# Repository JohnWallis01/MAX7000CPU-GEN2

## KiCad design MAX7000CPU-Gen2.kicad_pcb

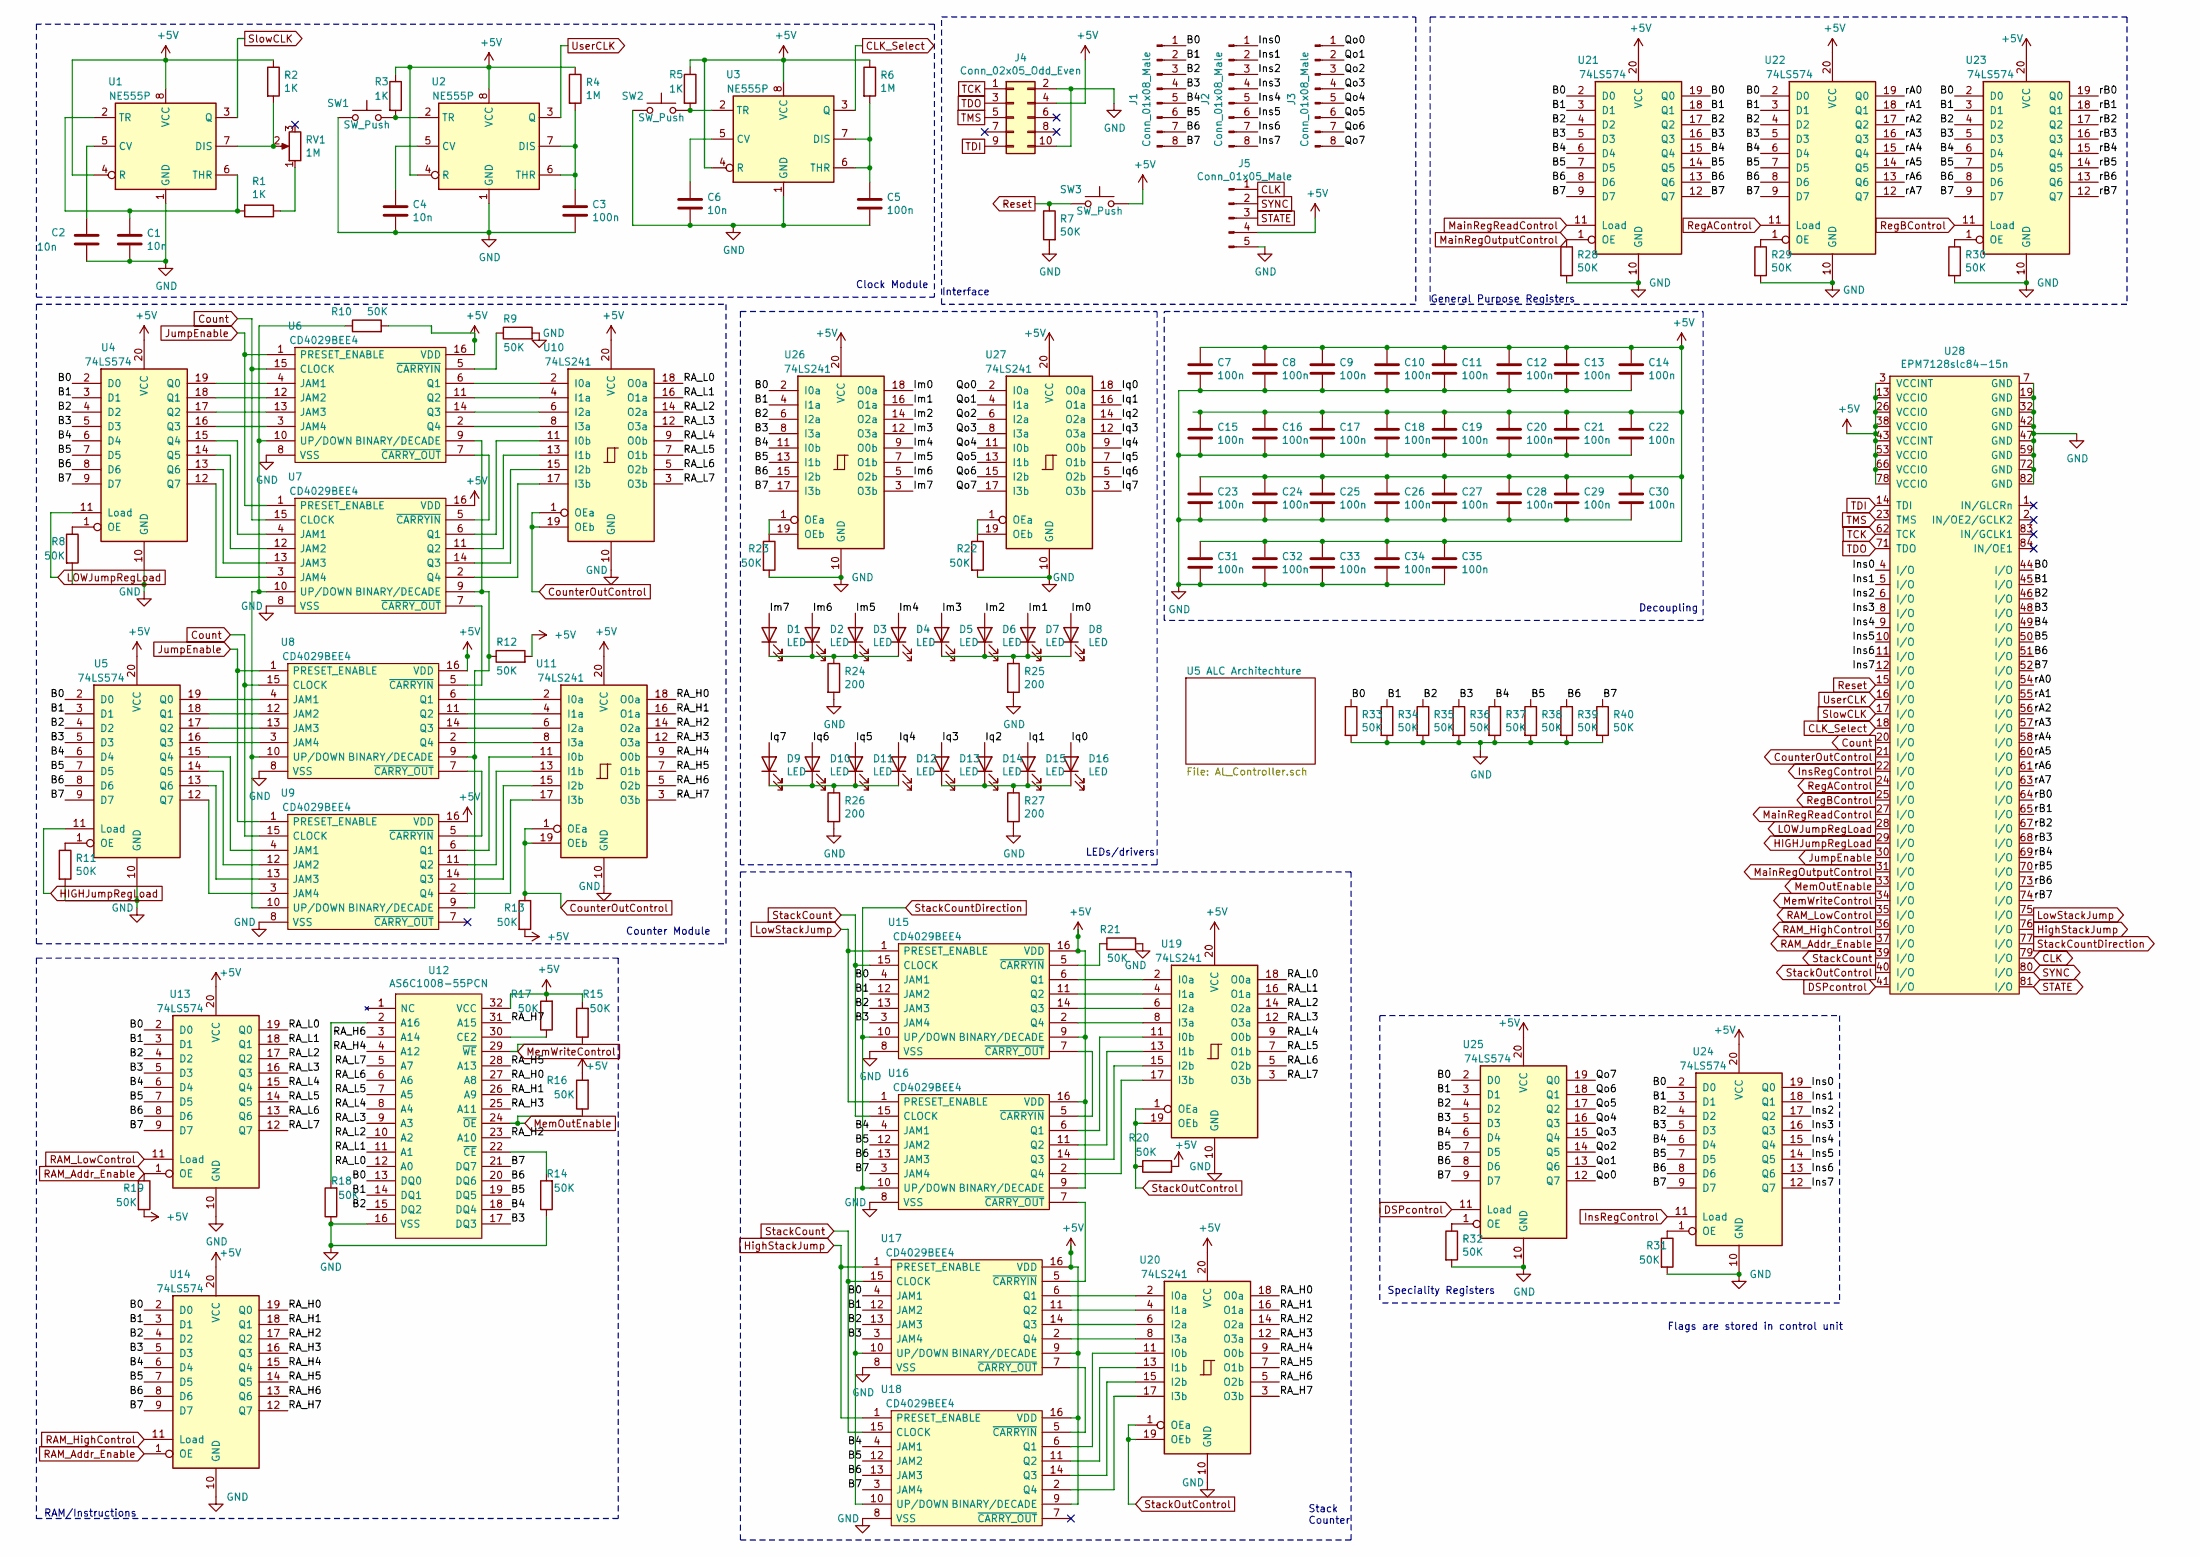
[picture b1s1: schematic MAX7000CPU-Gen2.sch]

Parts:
C1, C2, C4, C6: 10n; C_Disc_D5.0mm_W2.5mm_P2.50mm
C3, C5: 100n; C_Disc_D5.0mm_W2.5mm_P2.50mm
C7, C8, C9, C10, C11, C12, C13, C14, C15, C16, C17, C18, C19, C20, C21, C22, C23, C24, C25, C26, C27, C28, C29, C30, C31, C32, C33, C34, C35: 100n; C_0805_2012Metric_Pad1.18x1.45mm_HandSolder
D1, D2, D3, D4, D5, D6, D7, D8, D9, D10, D11, D12, D13, D14, D15, D16: LED; LED_D3.0mm
J1, J2, J3: Conn_01x08_Male; PinHeader_1x08_P2.54mm_Vertical
J4: Conn_02x05_Odd_Even; PinHeader_2x05_P2.54mm_Vertical
J5: Conn_01x05_Male; PinHeader_1x05_P2.54mm_Vertical
R1, R2, R3, R5: 1K; R_Axial_DIN0207_L6.3mm_D2.5mm_P7.62mm_Horizontal
R4, R6: 1M; R_Axial_DIN0207_L6.3mm_D2.5mm_P7.62mm_Horizontal
R7, R8, R9, R10, R11, R12, R13, R14, R15, R16, R17, R18, R19, R20, R21, R22, R23, R28, R29, R30, R31, R32, R33, R34, R35, R36, R37, R38, R39, R40: 50K; R_Axial_DIN0207_L6.3mm_D2.5mm_P7.62mm_Horizontal
R24, R25, R26, R27: 200; R_Axial_DIN0207_L6.3mm_D2.5mm_P7.62mm_Horizontal
RV1: 1M; SIP460W50P254L970H980Q3P
SW1, SW2, SW3: SW_Push; SW_PUSH_6mm
U1, U2, U3: NE555P; DIP-8_W7.62mm
U4, U5, U13, U14, U21, U22, U23, U24, U25: 74LS574; DIP-20_W7.62mm
U6, U7, U8, U9, U15, U16, U17, U18: CD4029BEE4; DIP-16_W7.62mm; Mouser Part Number 595-CD4029BEE4
U10, U11, U19, U20, U26, U27: 74LS241; DIP-20_W7.62mm
U12: AS6C1008-55PCN; DIP-32_W15.24mm; Mouser Part Number 913-AS6C1008-55PCN
U28: EPM7128slc84-15n; PLCC-84_THT-Socket

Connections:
+5V: C7.1, C8.1, C9.1, C10.1, C11.1, C12.1, C13.1, C14.1, C15.1, C16.1, C17.1, C18.1, C19.1, C20.1, C21.1, C22.1, C23.1, C24.1, C25.1, C26.1, C27.1, C28.1, C29.1, C30.1, C31.1, C32.1, C33.1, C34.1, C35.1, J4.4, J5.4, R2.1, R3.1, R4.1, R5.1, R6.1, R10.2, R12.2, R13.2, R15.2, R16.2, R17.2, R19.2, R20.2, SW3.2, U1.4 (R), U1.8 (VCC), U2.4 (R), U2.8 (VCC), U3.4 (R), U3.8 (VCC), U4.20 (VCC), U5.20 (VCC), U6.16 (VDD), U7.16 (VDD), U8.16 (VDD), U9.16 (VDD), U10.20 (VCC), U11.20 (VCC), U12.32 (VCC), U13.20 (VCC), U14.20 (VCC), U15.9 (BINARY/DECADE), U15.16 (VDD), U16.9 (BINARY/DECADE), U16.16 (VDD), U17.9 (BINARY/DECADE), U17.16 (VDD), U18.9 (BINARY/DECADE), U18.16 (VDD), U19.20 (VCC), U20.20 (VCC), U21.20 (VCC), U22.20 (VCC), U23.20 (VCC), U24.20 (VCC), U25.20 (VCC), U26.20 (VCC), U27.20 (VCC), U28.3 (VCCINT), U28.13 (VCCIO), U28.26 (VCCIO), U28.38 (VCCIO), U28.43 (VCCINT), U28.53 (VCCIO), U28.66 (VCCIO), U28.78 (VCCIO)
/B0: J1.1, R33.1, U4.2 (D0), U5.2 (D0), U12.13 (DQ0), U13.2 (D0), U14.2 (D0), U15.4 (JAM1), U17.4 (JAM1), U21.2 (D0), U21.19 (Q0), U22.2 (D0), U23.2, U24.2, U25.2 (D0), U26.2 (I0a), U28.44 (I/O); also elsewhere on the board
/B1: J1.2, R34.1, U4.3 (D1), U5.3 (D1), U12.14 (DQ1), U13.3 (D1), U14.3 (D1), U15.12 (JAM2), U17.12 (JAM2), U21.3 (D1), U21.18 (Q1), U22.3 (D1), U23.3 (GND), U24.3 (GND), U25.3 (D1), U26.4 (I1a), U28.45 (I/O)
/B2: J1.3, R35.1, U4.4 (D2), U5.4 (D2), U12.15 (DQ2), U13.4 (D2), U14.4 (D2), U15.13 (JAM3), U17.13 (JAM3), U21.4 (D2), U21.17 (Q2), U22.4 (D2), U23.4, U24.4, U25.4 (D2), U26.6 (I2a), U28.46 (I/O); also elsewhere on the board
/B3: J1.4, R36.1, U4.5 (D3), U5.5 (D3), U12.17 (DQ3), U13.5 (D3), U14.5 (D3), U15.3 (JAM4), U17.3 (JAM4), U21.5 (D3), U21.16 (Q3), U22.5 (D3), U23.5 (VCC), U24.5 (VCC), U25.5 (D3), U26.8 (I3a), U28.48 (I/O)
/B4: J1.5, R37.1, U4.6 (D4), U5.6 (D4), U12.18 (DQ4), U13.6 (D4), U14.6 (D4), U16.4 (JAM1), U18.4 (JAM1), U21.6 (D4), U21.15 (Q4), U22.6 (D4), U23.6 (D4), U24.6 (D4), U25.6 (D4), U26.11 (I0b), U28.49 (I/O)
/B5: J1.6, R38.1, U4.7 (D5), U5.7 (D5), U12.19 (DQ5), U13.7 (D5), U14.7 (D5), U16.12 (JAM2), U18.12 (JAM2), U21.7 (D5), U21.14 (Q5), U22.7 (D5), U23.7 (D5), U24.7 (D5), U25.7 (D5), U26.13 (I1b), U28.50 (I/O)
/B6: J1.7, R39.1, U4.8 (D6), U5.8 (D6), U12.20 (DQ6), U13.8 (D6), U14.8 (D6), U16.13 (JAM3), U18.13 (JAM3), U21.8 (D6), U21.13 (Q6), U22.8 (D6), U23.8 (D6), U24.8 (D6), U25.8 (D6), U26.15 (I2b), U28.51 (I/O)
/B7: J1.8, R40.1, U4.9 (D7), U5.9 (D7), U12.21 (DQ7), U13.9 (D7), U14.9 (D7), U16.3 (JAM4), U18.3 (JAM4), U21.9 (D7), U21.12 (Q7), U22.9 (D7), U23.9 (D7), U24.9 (D7), U25.9 (D7), U26.17 (I3b), U28.52 (I/O)
/Im0: D8.2 (A), U26.18 (O0a)
/Im1: D7.2 (A), U26.16 (O1a)
/Im2: D6.2 (A), U26.14 (O2a)
/Im3: D5.2 (A), U26.12 (O3a)
/Im4: D4.2 (A), U26.9 (O0b)
/Im5: D3.2 (A), U26.7 (O1b)
/Im6: D2.2 (A), U26.5 (O2b)
/Im7: D1.2 (A), U26.3 (O3b)
/Ins0: J2.1, U24.19 (Q0), U28.4 (I/O)
/Ins1: J2.2, U24.18 (Q1), U28.5 (I/O)
/Ins2: J2.3, U24.17 (Q2), U28.6 (I/O)
/Ins3: J2.4, U24.16 (Q3), U28.8 (I/O)
/Ins4: J2.5, U24.15 (Q4), U28.9 (I/O)
/Ins5: J2.6, U24.14 (Q5), U28.10 (I/O)
/Ins6: J2.7, U24.13 (Q6), U28.11 (I/O)
/Ins7: J2.8, U24.12 (Q7), U28.12 (I/O)
/Iq0: D16.2 (A), U27.18 (O0a)
/Iq1: D15.2 (A), U27.16 (O1a)
/Iq2: D14.2 (A), U27.14 (O2a)
/Iq3: D13.2 (A), U27.12 (O3a)
/Iq4: D12.2 (A), U27.9 (O0b)
/Iq5: D11.2 (A), U27.7 (O1b)
/Iq6: D10.2 (A), U27.5 (O2b)
/Iq7: D9.2 (A), U27.3 (O3b)
/Qo0: J3.1, U25.12 (Q7), U27.2 (I0a)
/Qo1: J3.2, U25.13 (Q6), U27.4 (I1a)
/Qo2: J3.3, U25.14 (Q5), U27.6 (I2a)
/Qo3: J3.4, U25.15 (Q4), U27.8 (I3a)
/Qo4: J3.5, U25.16 (Q3), U27.11 (I0b)
/Qo5: J3.6, U25.17 (Q2), U27.13 (I1b)
/Qo6: J3.7, U25.18 (Q1), U27.15 (I2b)
/Qo7: J3.8, U25.19 (Q0), U27.17 (I3b)
/RA_H0: U11.18 (O0a), U12.27 (A8), U14.19 (Q0), U20.18 (O0a)
/RA_H1: U11.16 (O1a), U12.26 (A9), U14.18 (Q1), U20.16 (O1a)
/RA_H2: U11.14 (O2a), U12.23 (A10), U14.17 (Q2), U20.14 (O2a)
/RA_H3: U11.12 (O3a), U12.25 (A11), U14.16 (Q3), U20.12 (O3a)
/RA_H4: U11.9 (O0b), U12.4 (A12), U14.15 (Q4), U20.9 (O0b)
/RA_H5: U11.7 (O1b), U12.28 (A13), U14.14 (Q5), U20.7 (O1b)
/RA_H6: U11.5 (O2b), U12.3 (A14), U14.13 (Q6), U20.5 (O2b)
/RA_H7: U11.3 (O3b), U12.31 (A15), U14.12 (Q7), U20.3 (O3b)
/RA_L0: U10.18 (O0a), U12.12 (A0), U13.19 (Q0), U19.18 (O0a)
/RA_L1: U10.16 (O1a), U12.11 (A1), U13.18 (Q1), U19.16 (O1a)
/RA_L2: U10.14 (O2a), U12.10 (A2), U13.17 (Q2), U19.14 (O2a)
/RA_L3: U10.12 (O3a), U12.9 (A3), U13.16 (Q3), U19.12 (O3a)
/RA_L4: U10.9 (O0b), U12.8 (A4), U13.15 (Q4), U19.9 (O0b)
/RA_L5: U10.7 (O1b), U12.7 (A5), U13.14 (Q5), U19.7 (O1b)
/RA_L6: U10.5 (O2b), U12.6 (A6), U13.13 (Q6), U19.5 (O2b)
/RA_L7: U10.3 (O3b), U12.5 (A7), U13.12 (Q7), U19.3 (O3b)
/rA0: U22.19 (Q0), U28.54 (I/O)
/rA1: U22.18 (Q1), U28.55 (I/O)
/rA2: U22.17 (Q2), U28.56 (I/O)
/rA3: U22.16 (Q3), U28.57 (I/O)
/rA4: U22.15 (Q4), U28.58 (I/O)
/rA5: U22.14 (Q5), U28.60 (I/O)
/rA6: U22.13 (Q6), U28.61 (I/O)
/rA7: U22.12 (Q7), U28.63 (I/O)
/rB0: U23.19 (Q0), U28.64 (I/O)
/rB1: U23.18 (Q1), U28.65 (I/O)
/rB2: U23.17 (Q2), U28.67 (I/O)
/rB3: U23.16 (Q3), U28.68 (I/O)
/rB4: U23.15 (Q4), U28.69 (I/O)
/rB5: U23.14 (Q5), U28.70 (I/O)
/rB6: U23.13 (Q6), U28.73 (I/O)
/rB7: U23.12 (Q7), U28.74 (I/O)
CLK: J5.1, U28.79 (I/O)
CLK_Select: U3.3 (Q), U28.18 (I/O)
Count: U6.15 (CLOCK), U7.15 (CLOCK), U8.15 (CLOCK), U9.15 (CLOCK), U28.20 (I/O)
CounterOutControl: R13.1, U10.1 (OEa), U10.19 (OEb), U11.1 (OEa), U11.19 (OEb), U28.21 (I/O)
DSPcontrol: U25.11 (Load), U28.41 (I/O)
GND: C1.2, C2.2, C3.2, C4.2, C5.2, C6.2, C7.2, C8.2, C9.2, C10.2, C11.2, C12.2, C13.2, C14.2, C15.2, C16.2, C17.2, C18.2, C19.2, C20.2, C21.2, C22.2, C23.2, C24.2, C25.2, C26.2, C27.2, C28.2, C29.2, C30.2, C31.2, C32.2, C33.2, C34.2, C35.2, J4.2, J4.10, J5.5, R7.2, R8.2, R9.2, R11.2, R14.1, R18.1, R21.2, R22.2, R23.2, R24.2, R25.2, R26.2, R27.2, R28.2, R29.2, R30.2, R31.2, R32.2, R33.2, R34.2, R35.2, R36.2, R37.2, R38.2, R39.2, R40.2, SW1.1, SW2.1, U1.1 (GND), U2.1 (GND), U3.1 (GND), U4.10 (GND), U5.10 (GND), U6.8 (VSS), U7.8 (VSS), U8.8 (VSS), U9.8 (VSS), U10.10 (GND), U11.10 (GND), U12.16 (VSS), U13.10 (GND), U14.10 (GND), U15.8 (VSS), U16.8 (VSS), U17.8 (VSS), U18.8 (VSS), U19.10 (GND), U20.10 (GND), U21.10 (GND), U22.10 (GND), U23.10 (GND), U24.10 (GND), U25.10 (GND), U26.10 (GND), U27.10 (GND), U28.7 (GND), U28.19 (GND), U28.32 (GND), U28.42 (GND), U28.47 (GND), U28.59 (GND), U28.72 (GND), U28.82 (GND)
HIGHJumpRegLoad: U5.11 (Load), U28.29 (I/O)
HighStackJump: U17.1 (PRESET_ENABLE), U18.1 (PRESET_ENABLE), U28.76 (I/O)
InsRegControl: U24.11 (Load), U28.22 (I/O)
JumpEnable: U6.1 (PRESET_ENABLE), U7.1 (PRESET_ENABLE), U8.1 (PRESET_ENABLE), U9.1 (PRESET_ENABLE), U28.30 (I/O)
LOWJumpRegLoad: U4.11 (Load), U28.28 (I/O)
LowStackJump: U15.1 (PRESET_ENABLE), U16.1 (PRESET_ENABLE), U28.75 (I/O)
MainRegOutputControl: R28.1, U21.1 (OE), U28.31 (I/O)
MainRegReadControl: U21.11 (Load), U28.27 (I/O)
MemOutEnable: R16.1, U12.24 (~OE), U28.33 (I/O)
MemWriteControl: R15.1, U12.29 (~WE), U28.34 (I/O)
unnamed: C1.1, R1.2, U1.2 (TR), U1.6 (THR)
unnamed: C2.1, U1.5 (CV)
unnamed: C3.1, R4.2, U2.6 (THR), U2.7 (DIS)
unnamed: C4.1, U2.5 (CV)
unnamed: C5.1, R6.2, U3.6 (THR), U3.7 (DIS)
unnamed: C6.1, U3.5 (CV)
unnamed: D1.1 (K), D2.1 (K), D3.1 (K), D4.1 (K), R24.1
unnamed: D5.1 (K), D6.1 (K), D7.1 (K), D8.1 (K), R25.1
unnamed: D9.1 (K), D10.1 (K), D11.1 (K), D12.1 (K), R26.1
unnamed: D13.1 (K), D14.1 (K), D15.1 (K), D16.1 (K), R27.1
unnamed: R1.1, RV1.1
unnamed: R2.2, RV1.2, U1.7 (DIS)
unnamed: R3.2, SW1.2, U2.2 (TR)
unnamed: R5.2, SW2.2, U3.2 (TR)
unnamed: R8.1, U4.1 (OE)
unnamed: R9.1, U6.5 (~CARRYIN)
unnamed: R10.1, U6.10 (UP/DOWN), U7.10 (UP/DOWN), U8.10 (UP/DOWN), U9.10 (UP/DOWN)
unnamed: R11.1, U5.1 (OE)
unnamed: R12.1, U6.9 (BINARY/DECADE), U7.9 (BINARY/DECADE), U8.9 (BINARY/DECADE), U9.9 (BINARY/DECADE)
unnamed: R14.2, U12.22 (~CE)
unnamed: R17.1, U12.30 (CE2)
unnamed: R18.2, U12.2 (A16)
unnamed: R21.1, U15.5 (~CARRYIN)
unnamed: R22.1, U27.1 (OEa), U27.19 (OEb)
unnamed: R23.1, U26.1 (OEa), U26.19 (OEb)
unnamed: R29.1, U22.1 (OE)
unnamed: R30.1, U23.1
unnamed 119: R31.1, U24.1; also elsewhere on the board
unnamed: R32.1, U25.1 (OE)
unnamed: U4.12 (Q7), U7.3 (JAM4)
unnamed: U4.13 (Q6), U7.13 (JAM3)
unnamed: U4.14 (Q5), U7.12 (JAM2)
unnamed: U4.15 (Q4), U7.4 (JAM1)
unnamed: U4.16 (Q3), U6.3 (JAM4)
unnamed: U4.17 (Q2), U6.13 (JAM3)
unnamed: U4.18 (Q1), U6.12 (JAM2)
unnamed: U4.19 (Q0), U6.4 (JAM1)
unnamed: U5.12 (Q7), U9.3 (JAM4)
unnamed: U5.13 (Q6), U9.13 (JAM3)
unnamed: U5.14 (Q5), U9.12 (JAM2)
unnamed: U5.15 (Q4), U9.4 (JAM1)
unnamed: U5.16 (Q3), U8.3 (JAM4)
unnamed: U5.17 (Q2), U8.13 (JAM3)
unnamed: U5.18 (Q1), U8.12 (JAM2)
unnamed: U5.19 (Q0), U8.4 (JAM1)
unnamed: U6.7 (~CARRY_OUT), U7.5 (~CARRYIN)
unnamed: U7.7 (~CARRY_OUT), U8.5 (~CARRYIN)
unnamed: U8.7 (~CARRY_OUT), U9.5 (~CARRYIN)
unnamed: U6.6 (Q1), U10.2 (I0a)
unnamed: U6.11 (Q2), U10.4 (I1a)
unnamed: U6.14 (Q3), U10.6 (I2a)
unnamed: U6.2 (Q4), U10.8 (I3a)
unnamed: U7.6 (Q1), U10.11 (I0b)
unnamed: U7.11 (Q2), U10.13 (I1b)
unnamed: U7.14 (Q3), U10.15 (I2b)
unnamed: U7.2 (Q4), U10.17 (I3b)
unnamed: U8.6 (Q1), U11.2 (I0a)
unnamed: U8.11 (Q2), U11.4 (I1a)
unnamed: U8.14 (Q3), U11.6 (I2a)
unnamed: U8.2 (Q4), U11.8 (I3a)
unnamed: U9.6 (Q1), U11.11 (I0b)
unnamed: U9.11 (Q2), U11.13 (I1b)
unnamed: U9.14 (Q3), U11.15 (I2b)
unnamed: U9.2 (Q4), U11.17 (I3b)
unnamed: U15.2 (Q4), U19.8 (I3a)
unnamed: U15.6 (Q1), U19.2 (I0a)
unnamed: U15.7 (~CARRY_OUT), U16.5 (~CARRYIN)
unnamed: U15.11 (Q2), U19.4 (I1a)
unnamed: U15.14 (Q3), U19.6 (I2a)
unnamed: U16.2 (Q4), U19.17 (I3b)
unnamed: U16.6 (Q1), U19.11 (I0b)
unnamed: U16.7 (~CARRY_OUT), U17.5 (~CARRYIN)
unnamed: U16.11 (Q2), U19.13 (I1b)
unnamed: U16.14 (Q3), U19.15 (I2b)
unnamed: U17.2 (Q4), U20.8 (I3a)
unnamed: U17.6 (Q1), U20.2 (I0a)
unnamed: U17.7 (~CARRY_OUT), U18.5 (~CARRYIN)
unnamed: U17.11 (Q2), U20.4 (I1a)
unnamed: U17.14 (Q3), U20.6 (I2a)
unnamed: U18.2 (Q4), U20.17 (I3b)
unnamed: U18.6 (Q1), U20.11 (I0b)
unnamed: U18.11 (Q2), U20.13 (I1b)
unnamed: U18.14 (Q3), U20.15 (I2b)
RAM_Addr_Enable: R19.1, U13.1 (OE), U14.1 (OE), U28.37 (I/O)
RAM_HighControl: U14.11 (Load), U28.36 (I/O)
RAM_LowControl: U13.11 (Load), U28.35 (I/O)
RegAControl: U22.11 (Load), U28.24 (I/O)
RegBControl: U23.11 (Load), U28.25 (I/O)
Reset: R7.1, SW3.1, U28.15 (I/O)
STATE: J5.3, U28.81 (I/O)
SYNC: J5.2, U28.80 (I/O)
SlowCLK: U1.3 (Q), U28.17 (I/O)
StackCount: U15.15 (CLOCK), U16.15 (CLOCK), U17.15 (CLOCK), U18.15 (CLOCK), U28.39 (I/O)
StackCountDirection: U15.10 (UP/DOWN), U16.10 (UP/DOWN), U17.10 (UP/DOWN), U18.10 (UP/DOWN), U28.77 (I/O)
StackOutControl: R20.1, U19.1 (OEa), U19.19 (OEb), U20.1 (OEa), U20.19 (OEb), U28.40 (I/O)
TCK: J4.1, U28.62 (TCK)
TDI: J4.9, U28.14 (TDI)
TDO: J4.3, U28.71 (TDO)
TMS: J4.5, U28.23 (TMS)
UserCLK: U2.3 (Q), U28.16 (I/O)

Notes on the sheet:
Clock Module
Counter Module
LEDs/drivers
General Purpose Registers
Interface
RAM/Instructions
Stack Counter
Speciality Registers
Flags are stored in control unit
Decoupling

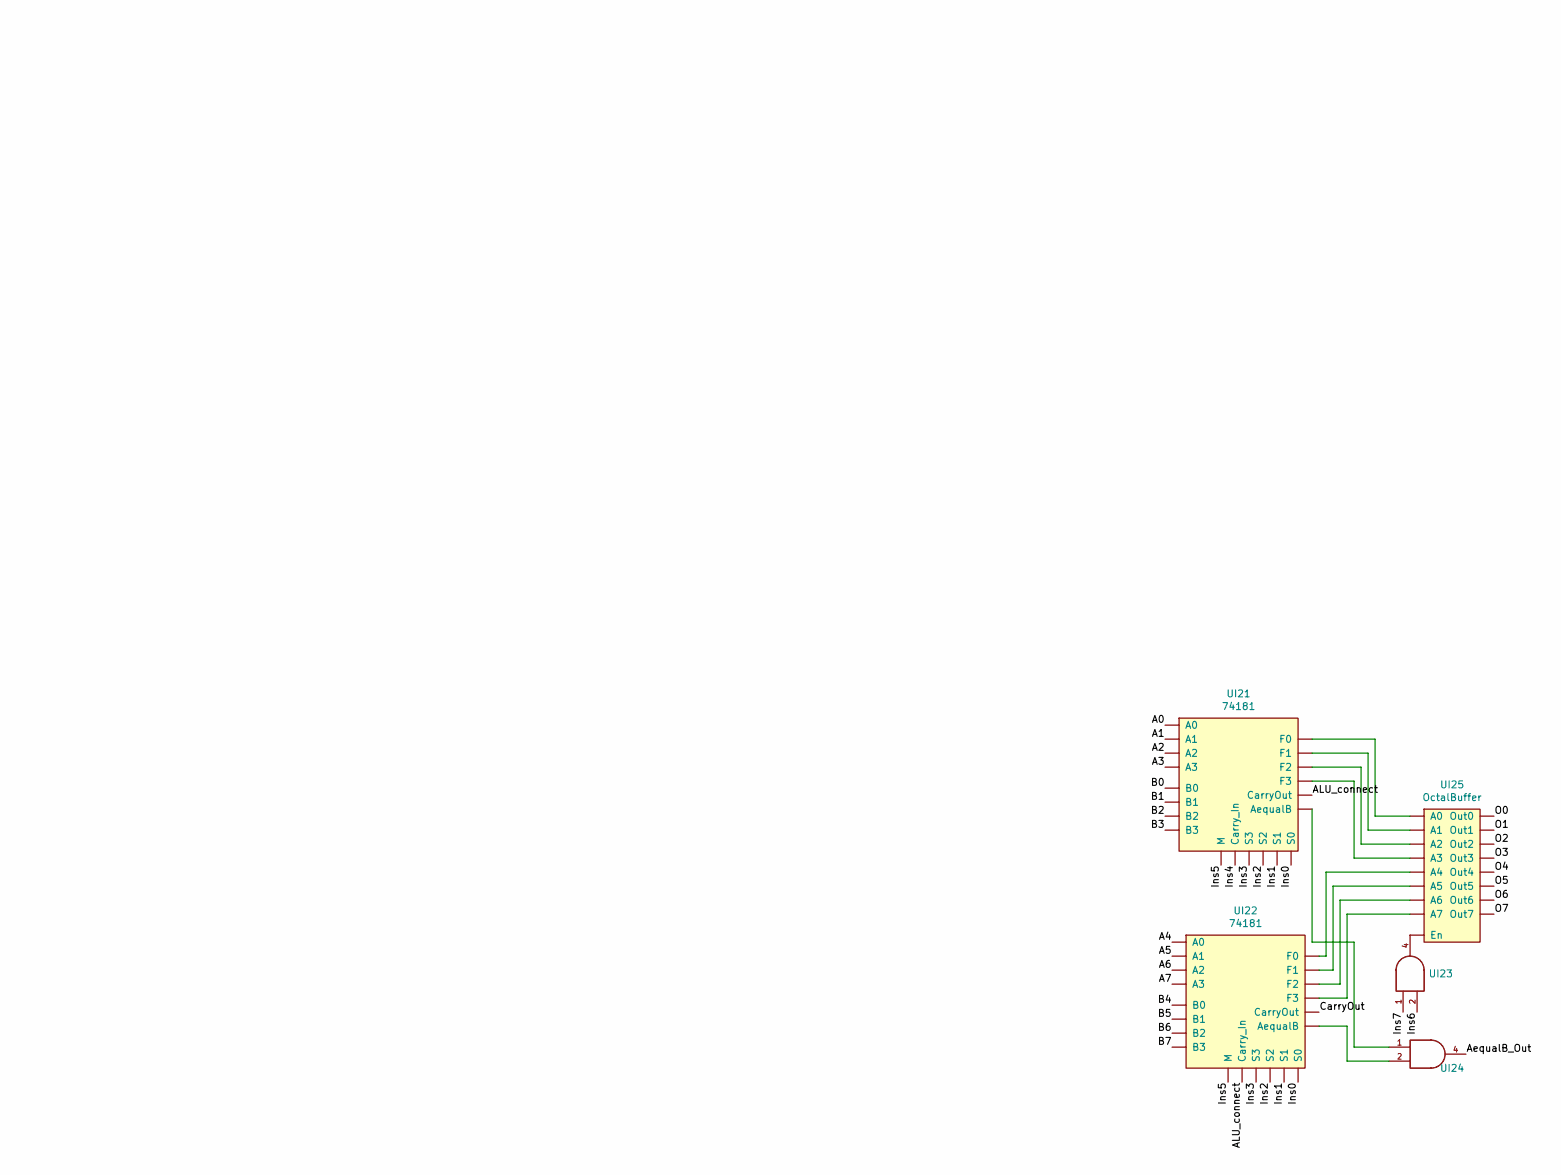
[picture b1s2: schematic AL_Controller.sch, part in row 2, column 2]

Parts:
U23: 74AHC1G08
U24: a
UI21, UI22: 74181
UI25: OctalBuffer

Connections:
/B0: U23.2, U24.2, UI22.~; also elsewhere on the board
/B1: U23.3 (GND), U24.3 (GND); also elsewhere on the board
/B2: U23.4, U24.4, UI25.~; also elsewhere on the board
/B3: U23.5 (VCC), U24.5 (VCC); also elsewhere on the board
unnamed 118: U23.1; also elsewhere on the board
unnamed 119: U24.1, UI21.~; also elsewhere on the board
unnamed: UI21.~, UI22.~, UI25.~
unnamed: UI22.~, UI25.~

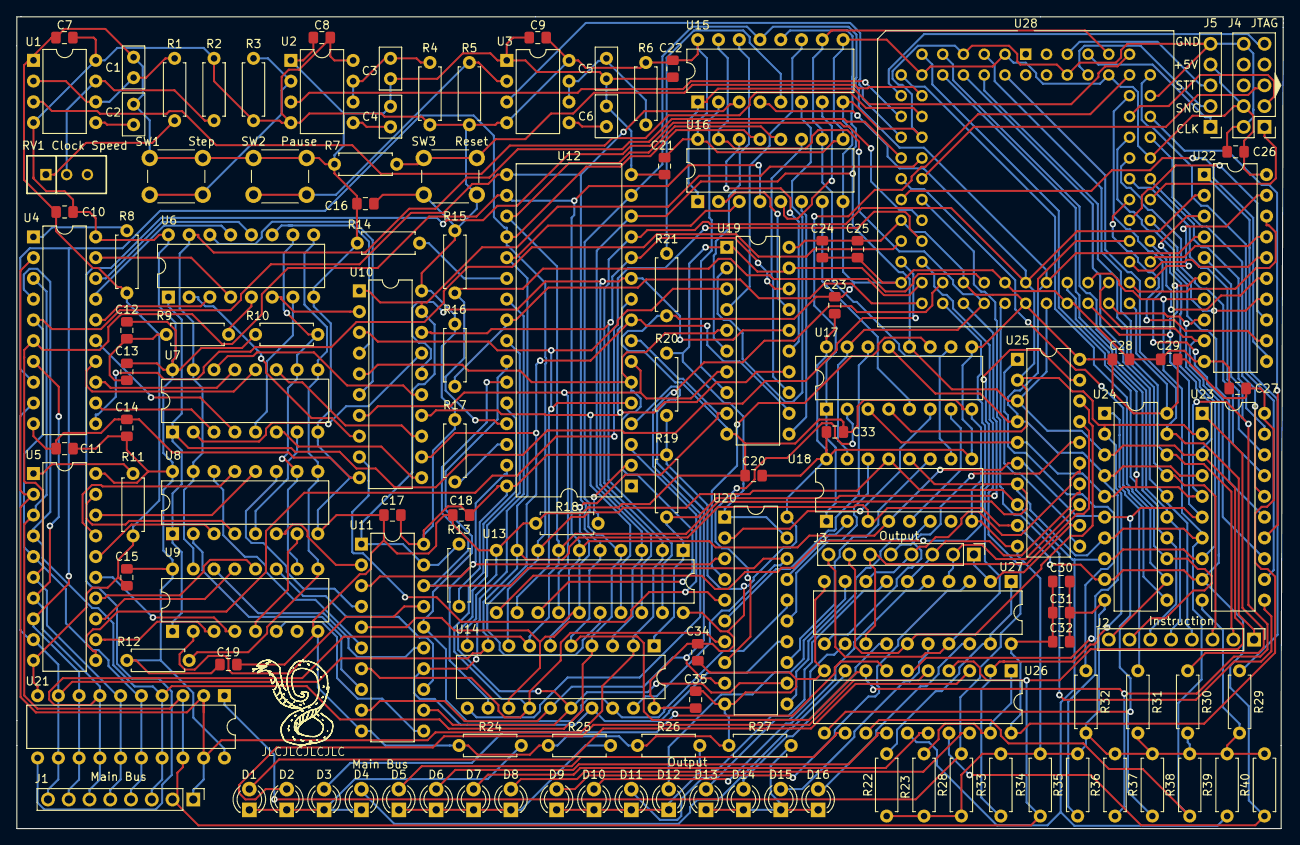
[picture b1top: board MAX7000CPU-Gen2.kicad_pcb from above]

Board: 2 copper layers, 154.9 x 99.3 mm, 128 parts (0 on the bottom side), 189 nets.

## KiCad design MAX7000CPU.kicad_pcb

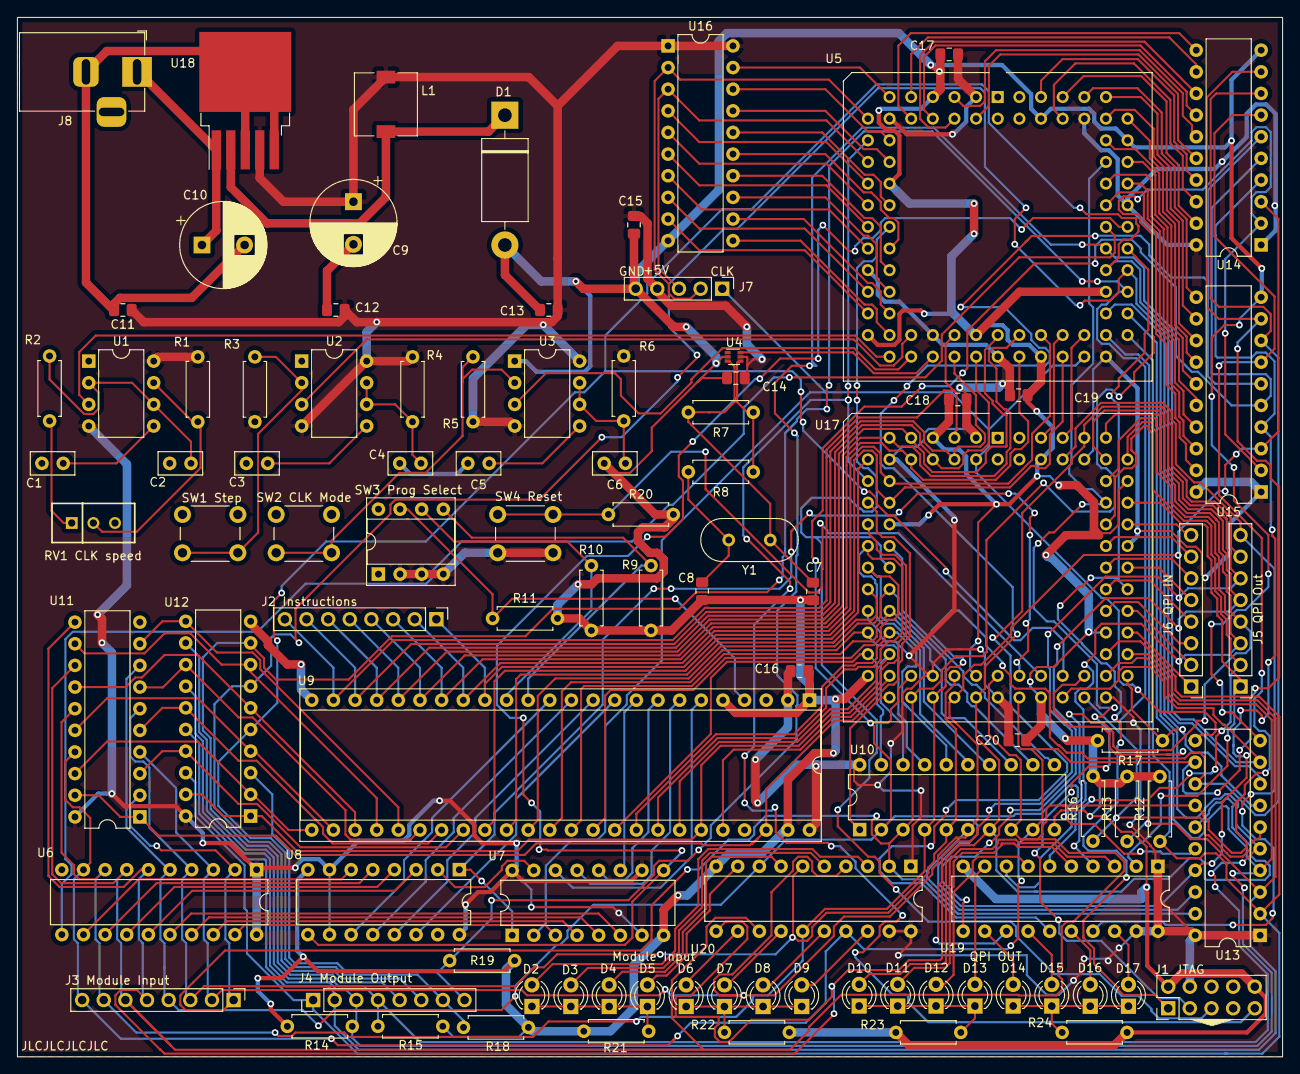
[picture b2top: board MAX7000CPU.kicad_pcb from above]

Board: 2 copper layers, 148.5 x 122.0 mm, 96 parts (0 on the bottom side), 170 nets.

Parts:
C1, C2, C3, C5: 10n; C_Disc_D5.0mm_W2.5mm_P2.50mm
C4, C6: 100n; C_Disc_D5.0mm_W2.5mm_P2.50mm
C7, C8: 32p; C_0805_2012Metric_Pad1.18x1.45mm_HandSolder
C9: 220u; CP_Radial_D10.0mm_P5.00mm
C10: 680u; CP_Radial_D10.0mm_P5.00mm
C11, C12, C13, C14, C15, C16, C17, C18, C19, C20: 100n; C_0805_2012Metric_Pad1.18x1.45mm_HandSolder
D1: 1N5822; D_DO-201AD_P15.24mm_Horizontal
D2, D3, D4, D5, D6, D7, D8, D9, D10, D11, D12, D13, D14, D15, D16, D17: LED; LED_D3.0mm
J1 JTAG: Conn_02x05_Odd_Even; PinHeader_2x05_P2.54mm_Vertical
J2 Instructions, J3 Module Input, J4 Module Output, J5 QPI Out, J6 QPI IN: Conn_01x08_Male; PinHeader_1x08_P2.54mm_Vertical
J7: Conn_01x05_Male; PinHeader_1x05_P2.54mm_Vertical
J8: Barrel_Jack; BarrelJack_Horizontal
L1: 33u; L_7.3x7.3_H3.5
R1, R2, R3, R5, R8: 1K; R_Axial_DIN0207_L6.3mm_D2.5mm_P7.62mm_Horizontal
R4, R6: 1M; R_Axial_DIN0207_L6.3mm_D2.5mm_P7.62mm_Horizontal
R7: 2.2M; R_Axial_DIN0207_L6.3mm_D2.5mm_P7.62mm_Horizontal
R9, R10, R11, R12, R13, R14, R15, R16, R17, R18, R19, R20: 50K; R_Axial_DIN0207_L6.3mm_D2.5mm_P7.62mm_Horizontal
R21, R22, R23, R24: 200; R_Axial_DIN0207_L6.3mm_D2.5mm_P7.62mm_Horizontal
RV1 CLK speed: 1M; SIP460W50P254L970H980Q3P
SW1 Step, SW2 CLK Mode, SW4 Reset: SW_Push; SW_PUSH_6mm
SW3 Prog Select: SW_DIP_x04; DIP-8_W7.62mm_Socket
U1, U2, U3: NE555P; DIP-8_W7.62mm
U4: CLVC1GX04MDRLREP; SOT-563
U5, U17: EPM7128slc84-15n; PLCC-84_THT-Socket
U6, U10, U13, U14, U15, U16: 74LS573; DIP-20_W7.62mm
U7, U8: SN74HC161N; DIP-16_W7.62mm
U9: IDT7132; DIP-48_W15.24mm_Socket
U11, U12, U19, U20: 74LS241; DIP-20_W7.62mm
U18: LM2596S-5; TO-263-5_TabPin3
Y1: Crystal; Crystal_HC49-4H_Vertical

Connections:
+5V: C9.1, C11.1, C12.1, C13.1, C14.1, C15.1, C16.1, C17.1, C18.1, C19.1, C20.1, J1 JTAG.4, J7.4, L1.1, R1.1, R3.1, R4.1, R5.1, R6.1, SW3 Prog Select.2, SW3 Prog Select.3, SW3 Prog Select.4, SW4 Reset.2, U1.4, U1.8, U2.4, U2.8, U3.4, U3.8, U4.5, U5.3, U5.13, U5.26, U5.38, U5.43, U5.53, U5.66, U5.78, U6.1, U6.20, U7.7, U7.10, U7.16, U8.7, U8.10, U8.16, U9.2, U9.48, U10.20, U11.20, U12.20, U13.1, U13.20, U14.1, U14.20, U15.1, U15.20, U16.1, U16.20, U17.3, U17.13, U17.26, U17.38, U17.43, U17.53, U17.66, U17.78, U18.4, U19.1, U19.19, U19.20, U20.1, U20.19, U20.20
/A0: U5.79, U14.19
/A1: U5.80, U14.18
/A2: U5.81, U14.17
/A3: U5.4, U14.16
/A4: U5.5, U14.15
/A5: U5.8, U14.14
/A6: U5.6, U14.13
/A7: U5.9, U14.12
/B0: U5.67, U15.19
/B1: U5.68, U15.18
/B2: U5.69, U15.17
/B3: U5.70, U15.16
/B4: U5.73, U15.15
/B5: U5.74, U15.14
/B6: U5.76, U15.13
/B7: U5.75, U15.12
/C0: U7.14, U9.6
/C1: U7.13, U9.7
/C2: U7.12, U9.8
/C3: U7.11, U9.9
/C4: U8.14, U9.10
/C5: U8.13, U9.11
/C6: U8.12, U9.12
/C7: U8.11, U9.13
/I0: J3 Module Input.1, U6.2, U10.3, U11.2, U13.19, U14.2, U15.2, U17.35, U20.2
/I1: J3 Module Input.2, U6.3, U10.6, U11.4, U13.18, U14.3, U15.3, U17.39, U20.4
/I2: J3 Module Input.3, U6.4, U10.5, U11.6, U13.17, U14.4, U15.4, U17.40, U20.6
/I3: J3 Module Input.4, U6.5, U10.2, U11.8, U13.16, U14.5, U15.5, U17.36, U20.8
/I4: J3 Module Input.5, U6.6, U10.7, U11.11, U13.15, U14.6, U15.6, U17.41, U20.11
/I5: J3 Module Input.6, U6.7, U10.8, U11.13, U13.14, U14.7, U15.7, U17.44, U20.13
/I6: J3 Module Input.7, U6.8, U10.4, U11.15, U13.13, U14.8, U15.8, U17.37, U20.15
/I7: J3 Module Input.8, U6.9, U10.9, U11.17, U13.12, U14.9, U15.9, U17.45, U20.17
/Im0: D9.2, U20.18
/Im1: D8.2, U20.16
/Im2: D7.2, U20.14
/Im3: D6.2, U20.12
/Im4: D5.2, U20.9
/Im5: D4.2, U20.7
/Im6: D3.2, U20.5
/Im7: D2.2, U20.3
/Ins0: J2 Instructions.1, U5.49, U9.16, U17.17
/Ins1: J2 Instructions.2, U5.48, U9.17, U17.15
/Ins2: J2 Instructions.3, U5.45, U9.18, U17.10
/Ins3: J2 Instructions.4, U5.46, U9.19, U17.11
/Ins4: J2 Instructions.5, U5.44, U9.20, U17.9
/Ins5: J2 Instructions.6, U5.41, U9.21, U17.8
/Ins6: J2 Instructions.7, U5.39, U9.22, U17.6
/Ins7: J2 Instructions.8, U5.40, U9.23, U17.5
/Iq0: D17.2, U19.18
/Iq1: D16.2, U19.16
/Iq2: D15.2, U19.14
/Iq3: D14.2, U19.12
/Iq4: D13.2, U19.9
/Iq5: D12.2, U19.7
/Iq6: D11.2, U19.5
/Iq7: D10.2, U19.3
/M0: U9.42, U10.18, U17.31
/M1: U9.41, U10.15, U17.20
/M2: U9.40, U10.16, U17.29
/M3: U9.39, U10.19, U17.30
/M4: U9.38, U10.14, U17.22
/M5: U9.37, U10.13, U17.27
/M6: U9.36, U10.17, U17.28
/M7: U9.35, U10.12, U17.25
/M8: U9.34, U17.24
/M9: U9.33, U17.12
/M10: U9.44, U17.34
/O0: J4 Module Output.1, R12.1, U5.54, U12.18, U13.2, U17.57
/O1: J4 Module Output.2, R13.1, U5.55, U12.16, U13.3, U17.56
/O2: J4 Module Output.3, R14.1, U5.56, U12.14, U13.4, U17.55
/O3: J4 Module Output.4, R15.1, U5.57, U12.12, U13.5, U17.52
/O4: J4 Module Output.5, R16.1, U5.58, U12.9, U13.6, U17.51
/O5: J4 Module Output.6, R17.1, U5.60, U12.7, U13.7, U17.54
/O6: J4 Module Output.7, R18.1, U5.61, U12.5, U13.8, U17.50
/O7: J4 Module Output.8, R19.1, U5.63, U12.3, U13.9, U17.49
/P1: R9.1, SW3 Prog Select.5, U9.14
/P2: R10.1, SW3 Prog Select.6, U9.15
/P3: R11.1, SW3 Prog Select.7, U9.4
/Qi0: J6 QPI IN.1, U17.58
/Qi1: J6 QPI IN.2, U17.60
/Qi2: J6 QPI IN.3, U17.61
/Qi3: J6 QPI IN.4, U17.63
/Qi4: J6 QPI IN.5, U17.64
/Qi5: J6 QPI IN.6, U17.65
/Qi6: J6 QPI IN.7, U17.67
/Qi7: J6 QPI IN.8, U17.68
/Qo0: J5 QPI Out.1, U17.70, U19.2
/Qo1: J5 QPI Out.2, U17.69, U19.4
/Qo2: J5 QPI Out.3, U17.74, U19.6
/Qo3: J5 QPI Out.4, U17.73, U19.8
/Qo4: J5 QPI Out.5, U17.75, U19.11
/Qo5: J5 QPI Out.6, U17.76, U19.13
/Qo6: J5 QPI Out.7, U17.77, U19.15
/Qo7: J5 QPI Out.8, U17.80, U19.17
A=B_FlagIn: U5.15, U16.18
A=B_Out: J7.3, U5.16, U16.3
CLK: J7.1, U5.51, U7.2, U13.11, U17.4
CLK_Select: U3.3, U5.35
CarryFlagIn: U5.11, U16.19
CarryOut: J7.2, U5.12, U16.2
Comm0: U5.50, U17.81
Comm1: U5.52, U17.79
CounterReset: U7.1, U8.1, U17.46
FastCLK: U4.6, U5.37
Flag0In: U5.17, U16.17
Flag0Out: U5.18, U16.4
Flag1In: U5.21, U16.16
Flag1Out: U5.20, U16.5
Flag2In: U5.25, U16.15
Flag2Out: U5.22, U16.6
Flag3In: U5.27, U16.14
Flag3Out: U5.24, U16.7
Flag4In: U5.29, U16.13
Flag4Out: U5.28, U16.8
Flag5In: U5.31, U16.12
Flag5Out: U5.30, U16.9
FlagCLK: U5.34, U16.11
GND: C1.2, C2.2, C3.2, C4.2, C5.2, C6.2, C7.2, C8.2, C9.2, C10.2, C11.2, C12.2, C13.2, C14.2, C15.2, C16.2, C17.2, C18.2, C19.2, C20.2, D1.2, J1 JTAG.2, J1 JTAG.10, J7.5, J8.2, R9.2, R10.2, R11.2, R12.2, R13.2, R14.2, R15.2, R16.2, R17.2, R18.2, R19.2, R20.2, R21.2, R22.2, R23.2, R24.2, SW1 Step.1, SW2 CLK Mode.1, U1.1, U2.1, U3.1, U4.2, U5.7, U5.19, U5.32, U5.42, U5.47, U5.59, U5.72, U5.82, U6.10, U7.8, U8.8, U9.1, U9.5, U9.24, U9.47, U10.10, U11.10, U12.10, U13.10, U14.10, U15.10, U16.10, U17.7, U17.19, U17.32, U17.42, U17.47, U17.59, U17.72, U17.82, U18.3, U18.5, U19.10, U20.10
JumpEnable: U5.64, U7.9, U8.9
JumpRegLoad: U5.65, U6.11
MemOutControl: U9.43, U12.1, U12.19, U17.18
MemWriteControl: U9.46, U11.1, U11.19, U17.16
unnamed: C1.1, U1.5
unnamed: C2.1, R2.2, U1.2, U1.6
unnamed: C3.1, U2.5
unnamed: C4.1, R4.2, U2.6, U2.7
unnamed: C5.1, U3.5
unnamed: C6.1, R6.2, U3.6, U3.7
unnamed: C7.1, R7.2, U4.3, Y1.1
unnamed: C8.1, R8.2, Y1.2
unnamed: C10.1, J8.1, U18.1
unnamed: D1.1, L1.2, U18.2
unnamed: D2.1, D3.1, D4.1, D5.1, R21.1
unnamed: D6.1, D7.1, D8.1, D9.1, R22.1
unnamed: D10.1, D11.1, D12.1, D13.1, R23.1
unnamed: D14.1, D15.1, D16.1, D17.1, R24.1
unnamed: R1.2, RV1 CLK speed.2, U1.7
unnamed: R2.1, RV1 CLK speed.1
unnamed: R3.2, SW1 Step.2, U2.2
unnamed: R5.2, SW2 CLK Mode.2, U3.2
unnamed: R7.1, R8.1, U4.4
unnamed: U6.12, U8.6
unnamed: U6.13, U8.5
unnamed: U6.14, U8.4
unnamed: U6.15, U8.3
unnamed: U6.16, U7.6
unnamed: U6.17, U7.5
unnamed: U6.18, U7.4
unnamed: U6.19, U7.3
unnamed: U7.15, U8.2
unnamed: U9.32, U11.3, U12.17
unnamed: U9.31, U11.5, U12.15
unnamed: U9.30, U11.7, U12.13
unnamed: U9.29, U11.9, U12.11
unnamed: U9.28, U11.12, U12.8
unnamed: U9.27, U11.14, U12.6
unnamed: U9.26, U11.16, U12.4
unnamed: U9.25, U11.18, U12.2
RamAddrEnable: U10.1, U17.33
RamAddrLoad: U10.11, U17.21
RegAControl: U5.10, U14.11
RegBControl: U5.77, U15.11
Reset: R20.1, SW4 Reset.1, U17.48
SlowCLK: U1.3, U5.33
TCK: J1 JTAG.1, U5.62, U17.62
TDI: J1 JTAG.9, U5.14, U17.14
TDO: J1 JTAG.3, U5.71, U17.71
TMS: J1 JTAG.5, U5.23, U17.23
UserCLK: U2.3, U5.36

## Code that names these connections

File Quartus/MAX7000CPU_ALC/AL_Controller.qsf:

# -------------------------------------------------------------------------- #
#
# Copyright (C) 1991-2013 Altera Corporation
# Your use of Altera Corporation's design tools, logic functions 
# and other software and tools, and its AMPP partner logic 
# functions, and any output files from any of the foregoing 
# (including device programming or simulation files), and any 
# associated documentation or information are expressly subject 
# to the terms and conditions of the Altera Program License 
# Subscription Agreement, Altera MegaCore Function License 
# Agreement, or other applicable license agreement, including, 
# without limitation, that your use is for the sole purpose of 
# programming logic devices manufactured by Altera and sold by 
# Altera or its authorized distributors.  Please refer to the 
# applicable agreement for further details.
#
# -------------------------------------------------------------------------- #
#
# Quartus II 64-Bit
# Version 13.0.1 Build 232 06/12/2013 Service Pack 1 SJ Web Edition
# Date created = 16:56:51  July 19, 2021
#
# -------------------------------------------------------------------------- #
#
# Notes:
#
# 1) The default values for assignments are stored in the file:
#		AL_Controller_assignment_defaults.qdf
#    If this file doesn't exist, see file:
#		assignment_defaults.qdf
#
# 2) Altera recommends that you do not modify this file. This
#    file is updated automatically by the Quartus II software
#    and any changes you make may be lost or overwritten.
#
# -------------------------------------------------------------------------- #


set_global_assignment -name FAMILY MAX7000S
set_global_assignment -name DEVICE "EPM7128SLC84-15"
set_global_assignment -name TOP_LEVEL_ENTITY AL_Controller
set_global_assignment -name ORIGINAL_QUARTUS_VERSION "13.0 SP1"
set_global_assignment -name PROJECT_CREATION_TIME_DATE "16:56:51  JULY 19, 2021"
set_global_assignment -name LAST_QUARTUS_VERSION "13.0 SP1"
set_global_assignment -name PROJECT_OUTPUT_DIRECTORY output_files
set_global_assignment -name DEVICE_FILTER_PACKAGE PLCC
set_global_assignment -name DEVICE_FILTER_PIN_COUNT 84
set_global_assignment -name DEVICE_FILTER_SPEED_GRADE 15
set_global_assignment -name ERROR_CHECK_FREQUENCY_DIVISOR "-1"
set_global_assignment -name EDA_DESIGN_ENTRY_SYNTHESIS_TOOL "Design Compiler"
set_global_assignment -name EDA_INPUT_VCC_NAME VDD -section_id eda_design_synthesis
set_global_assignment -name EDA_LMF_FILE altsyn.lmf -section_id eda_design_synthesis
set_global_assignment -name EDA_INPUT_DATA_FORMAT VHDL -section_id eda_design_synthesis
set_global_assignment -name EDA_SIMULATION_TOOL "ModelSim (VHDL)"
set_global_assignment -name EDA_TIME_SCALE "1 ps" -section_id eda_simulation
set_global_assignment -name EDA_OUTPUT_DATA_FORMAT VHDL -section_id eda_simulation
set_global_assignment -name MAX7000_DEVICE_IO_STANDARD TTL
set_location_assignment PIN_74 -to regB[7]
set_location_assignment PIN_73 -to regB[6]
set_location_assignment PIN_70 -to regB[5]
set_location_assignment PIN_69 -to regB[4]
set_location_assignment PIN_68 -to regB[3]
set_location_assignment PIN_67 -to regB[2]
set_location_assignment PIN_65 -to regB[1]
set_location_assignment PIN_64 -to regB[0]
set_location_assignment PIN_63 -to regA[7]
set_location_assignment PIN_61 -to regA[6]
set_location_assignment PIN_60 -to regA[5]
set_location_assignment PIN_58 -to regA[4]
set_location_assignment PIN_57 -to regA[3]
set_location_assignment PIN_56 -to regA[2]
set_location_assignment PIN_55 -to regA[1]
set_location_assignment PIN_54 -to regA[0]
set_location_assignment PIN_16 -to UserCLK
set_location_assignment PIN_23 -to TMS
set_location_assignment PIN_14 -to TDI
set_location_assignment PIN_52 -to MainBus[7]
set_location_assignment PIN_51 -to MainBus[6]
set_location_assignment PIN_50 -to MainBus[5]
set_location_assignment PIN_49 -to MainBus[4]
set_location_assignment PIN_48 -to MainBus[3]
set_location_assignment PIN_46 -to MainBus[2]
set_location_assignment PIN_45 -to MainBus[1]
set_location_assignment PIN_44 -to MainBus[0]
set_location_assignment PIN_62 -to TCK
set_location_assignment PIN_17 -to SlowCLK
set_location_assignment PIN_15 -to Reset
set_location_assignment PIN_12 -to Ins[7]
set_location_assignment PIN_11 -to Ins[6]
set_location_assignment PIN_10 -to Ins[5]
set_location_assignment PIN_9 -to Ins[4]
set_location_assignment PIN_8 -to Ins[3]
set_location_assignment PIN_6 -to Ins[2]
set_location_assignment PIN_5 -to Ins[1]
set_location_assignment PIN_4 -to Ins[0]
set_location_assignment PIN_18 -to CLK_Select
set_location_assignment PIN_71 -to TDO
set_location_assignment PIN_40 -to StackOutControl
set_location_assignment PIN_39 -to StackCount
set_location_assignment PIN_80 -to SYNC
set_location_assignment PIN_81 -to STATE
set_location_assignment PIN_25 -to RegBControl
set_location_assignment PIN_24 -to RegAControl
set_location_assignment PIN_35 -to Ram_LowControl
set_location_assignment PIN_36 -to Ram_HighControl
set_location_assignment PIN_37 -to Ram_Addr_Enable
set_location_assignment PIN_34 -to MemWriteControl
set_location_assignment PIN_33 -to MemOutEnable
set_location_assignment PIN_27 -to MainRegReadControl
set_location_assignment PIN_31 -to MainRegOutputControl
set_location_assignment PIN_75 -to LowStackJump
set_location_assignment PIN_28 -to LowJumpRegLoad
set_location_assignment PIN_30 -to JumpEnable
set_location_assignment PIN_22 -to InsRegControl
set_location_assignment PIN_76 -to HighStackJump
set_location_assignment PIN_29 -to HighJumpRegLoad
set_location_assignment PIN_41 -to DisplayControl
set_location_assignment PIN_21 -to CounterOutControl
set_location_assignment PIN_20 -to Count
set_location_assignment PIN_79 -to CLK
set_global_assignment -name OPTIMIZE_HOLD_TIMING OFF
set_global_assignment -name OPTIMIZE_MULTI_CORNER_TIMING OFF
set_global_assignment -name FITTER_EFFORT "STANDARD FIT"
set_location_assignment PIN_77 -to StackCountDirection
set_global_assignment -name VHDL_FILE "VHDL files/KeyDecoder.vhdl"
set_global_assignment -name VHDL_FILE "VHDL files/MicroCodeGen.vhdl"
set_global_assignment -name VERILOG_FILE "VHDL files/ALU.verilog"
set_global_assignment -name VHDL_FILE "VHDL files/logic.vhdl"
set_global_assignment -name VHDL_FILE "VHDL files/ALC.vhdl"
